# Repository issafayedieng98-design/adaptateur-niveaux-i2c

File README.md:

# Adaptateur de Niveaux Logiques I2C — 3,3 V ↔ 5 V

Carte PCB sur mesure conçue sous **KiCad 8** permettant la conversion bidirectionnelle d'un bus I2C entre deux niveaux de tension (**3,3 V ↔ 5 V**), au format breadboard.

## Objectif

Permettre la communication entre un microcontrôleur 3,3 V (STM32, ESP32, RP2040…) et des périphériques I2C alimentés en 5 V (afficheurs LCD, capteurs, etc.) sans risque de destruction des entrées.

## Caractéristiques

- Conversion bidirectionnelle I2C sur les lignes **SDA et SCL**
- Compatible **3,3 V ↔ 5 V**
- Format adapté à une utilisation sur **breadboard**
- Conception schématique et routage PCB complets sous KiCad 8
- PCB 2 couches

## Stack technique

## Fichiers du projet

| Fichier | Description |
|---|---|
| `adaptateur-niveaux-i2c.kicad_pro` | Fichier projet KiCad |
| `adaptateur-niveaux-i2c.kicad_sch` | Schéma électronique |
| `adaptateur-niveaux-i2c.kicad_pcb` | Routage PCB |
| `adaptateur-niveaux-i2c.kicad_sym` | Bibliothèque de symboles personnalisée |

## Auteur

**Issa FAYE** — Ingénieur Électronique & Systèmes Embarqués  
[Portfolio](https://issa-faye-portfolio.netlify.app)

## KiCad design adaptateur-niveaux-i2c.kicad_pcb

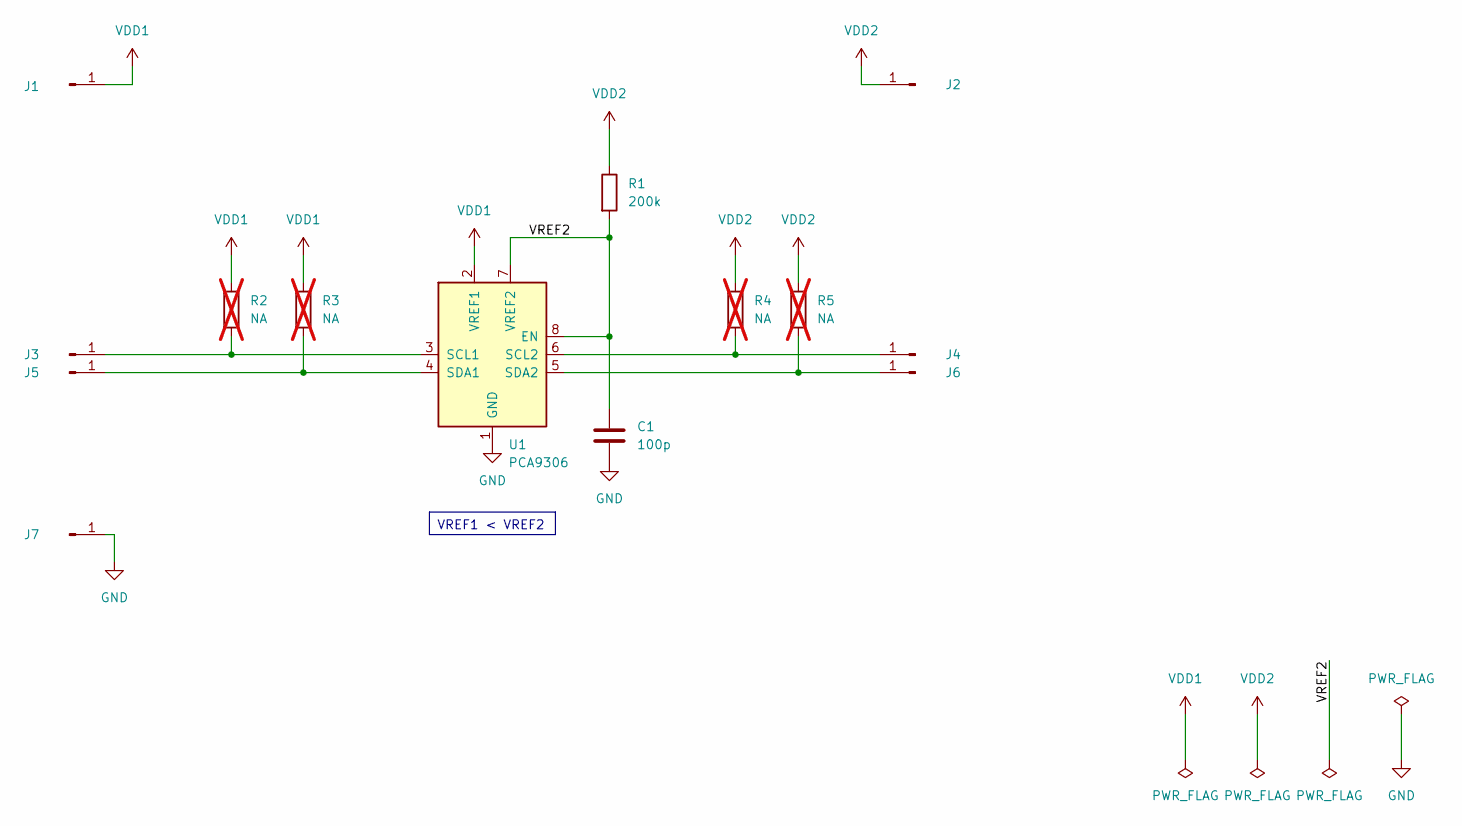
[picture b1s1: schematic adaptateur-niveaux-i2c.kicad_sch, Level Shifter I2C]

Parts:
C1: 100p; C_0603_1608Metric
J1, J2, J3, J4, J5, J6, J7: Conn_01x01_Pin; PinHeader_1x01_P2.54mm_Vertical
R1: 200k; R_0603_1608Metric
R2, R3, R4, R5: NA; R_0603_1608Metric; not fitted
U1: PCA9306; SSOP-8_2.95x2.8mm_P0.65mm

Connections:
/VREF2: C1.1, R1.2, U1.7 (VREF2), U1.8 (EN)
GND: C1.2, J7.1, U1.1 (GND)
unnamed: J3.1, R2.2, U1.3 (SCL1)
unnamed: J4.1, R4.2, U1.6 (SCL2)
unnamed: J5.1, R3.2, U1.4 (SDA1)
unnamed: J6.1, R5.2, U1.5 (SDA2)
VDD1: J1.1, R2.1, R3.1, U1.2 (VREF1)
VDD2: J2.1, R1.1, R4.1, R5.1

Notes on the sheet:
VREF1 < VREF2

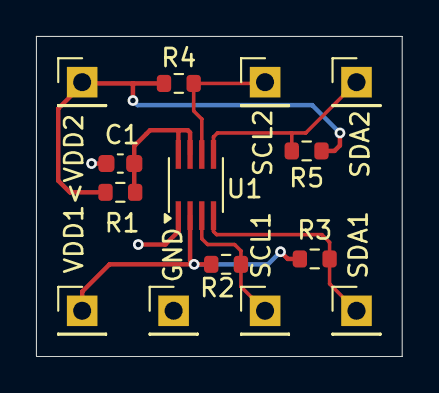
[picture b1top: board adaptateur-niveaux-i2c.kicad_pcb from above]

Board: 2 copper layers, 20.3 x 17.8 mm, 14 parts (0 on the bottom side), 8 nets.

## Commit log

2026-06-24 PCB Adaptateur I2C Level Shifter — KiCad 8
2026-06-26 Renommage complet en français : adaptateur-niveaux-i2c + README mis à jour
